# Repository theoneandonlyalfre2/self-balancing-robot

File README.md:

# Self-Balancing Robot

Robot autoequilibrado en desarrollo, con PCB propia, diseño mecánico en Fusion 360 y herramientas de control y visualización. Proyecto personal de **Alfredo Waugh Tocornal**.

Este repositorio reúne el diseño electrónico, los modelos CAD y los ensayos de firmware y software disponibles al 15 de octubre de 2026. La integración completa y la demostración de equilibrio autónomo están pendientes de validación.

*Vista del diseño CAD. No corresponde a una fotografía de un prototipo físico terminado.*

## Qué contiene

| Área | Trabajo disponible | Archivos |
|---|---|---|
| Electrónica | Esquema y PCB de dos capas en KiCad 10; ESP32-S3, TMC2209 y BNO085 en el esquema | [Proyecto KiCad](hardware/kicad), [vista de la PCB](docs/pcb-front.svg) |
| Mecánica | Base para motores NEMA 17 y encoders AS5600, plataforma para PCB, columnas y separadores | [Base de motores](mechanical/motor-base), [plataforma PCB](mechanical/pcb-deck) |
| Lectura de orientación | Firmware BNO085 y visualizador 3D de cuaterniones | [Firmware IMU](firmware/bno085), [visualizador Python](software/imu_visualizer.py) |
| Control experimental | Ensayo de control proporcional de un motor con medición de roll y ajuste desde una interfaz Qt | [Firmware de ensayo](firmware/nemamasimu), [interfaz](software/roll_controller.py) |
| Motores y encoders | Prueba independiente de dos TMC2209 y dos AS5600 con ESP32-S3 | [Prueba de banco](firmware/prueba_nema17_as5600) |
| Fabricación | Exportaciones históricas Gerber y taladros, STEP, STL y archivos Fusion 360 | [Gerbers](hardware/manufacturing), [CAD](mechanical) |

## Estado de desarrollo

- Diseño de circuito, ruteo de PCB, símbolos y huellas personalizados disponibles.
- Archivos CAD editables y exportaciones para inspeccionar la integración mecánica.
- Código de ensayos de lectura de IMU, control proporcional y movimiento de motores.
- Pendiente: unificar firmware, comprobar su correspondencia con el pinout de la PCB y validar el conjunto físico.
- Pendiente: registrar pruebas, resultados y un video del robot manteniendo el equilibrio.

Los programas son ensayos separados. `nemamasimu` describe un motor con A4988; la PCB utiliza dos TMC2209. No se ha establecido que esos ensayos puedan cargarse directamente en la PCB sin adaptar sus pines y configuración. El ensayo de dos motores tiene su propio cableado, documentado en su carpeta.

## Abrir el diseño

En **KiCad 10**, abre `hardware/kicad/Circuito Self-Balancing Robot.kicad_pro`. Se incluyen las huellas locales y dos bibliotecas de símbolos del proyecto. El esquema conserva sus símbolos embebidos. La edición de símbolos `PCM_Espressif` y los modelos 3D estándar pueden requerir instalar las bibliotecas correspondientes en tu equipo.

En **Autodesk Fusion 360**, importa los `.f3d` de `mechanical/`. Los `.step` permiten consultar la geometría en otros programas; los `.stl` corresponden a piezas individuales. Las instrucciones y dimensiones se encuentran en el `LEEME.md` de cada conjunto.

Los archivos de fabricación se conservan como exportaciones de trabajo del 5 de octubre. El PCB editable fue guardado después; no se asume que las exportaciones correspondan exactamente a su estado final. Consulta [las notas de fabricación](hardware/manufacturing/README.md).

## Usar el software

Consulta [software/README.md](software/README.md) para instalar dependencias, seleccionar el puerto serie y elegir la pareja de firmware e interfaz adecuada. El código de los ensayos se conserva sin modificar su lógica de control.

## Documentación

- [Arquitectura y protocolos](docs/architecture.md)
- [Estado y verificaciones](docs/status.md)
- [Procedencia de los archivos](docs/provenance.md)
- [Inventario con hashes SHA-256](docs/source-manifest.csv)
- [Atribuciones y componentes externos](THIRD_PARTY.md)

## Próximos hitos

1. Consolidar la asignación de pines y el firmware para la PCB.
2. Validar alimentación, sensores, drivers y mecánica del conjunto.
3. Integrar y ajustar el control de equilibrio con ambos motores.
4. Añadir registros de pruebas, fotografías del montaje y un video demostrativo.

## Autoría

Alfredo Waugh Tocornal. [LinkedIn](https://www.linkedin.com/in/alfredo-waugh-tocornal-26b0122b6).

Este repositorio no establece una licencia general de redistribución. Las bibliotecas y los diseños de terceros mantienen sus condiciones originales; consulta `THIRD_PARTY.md`.

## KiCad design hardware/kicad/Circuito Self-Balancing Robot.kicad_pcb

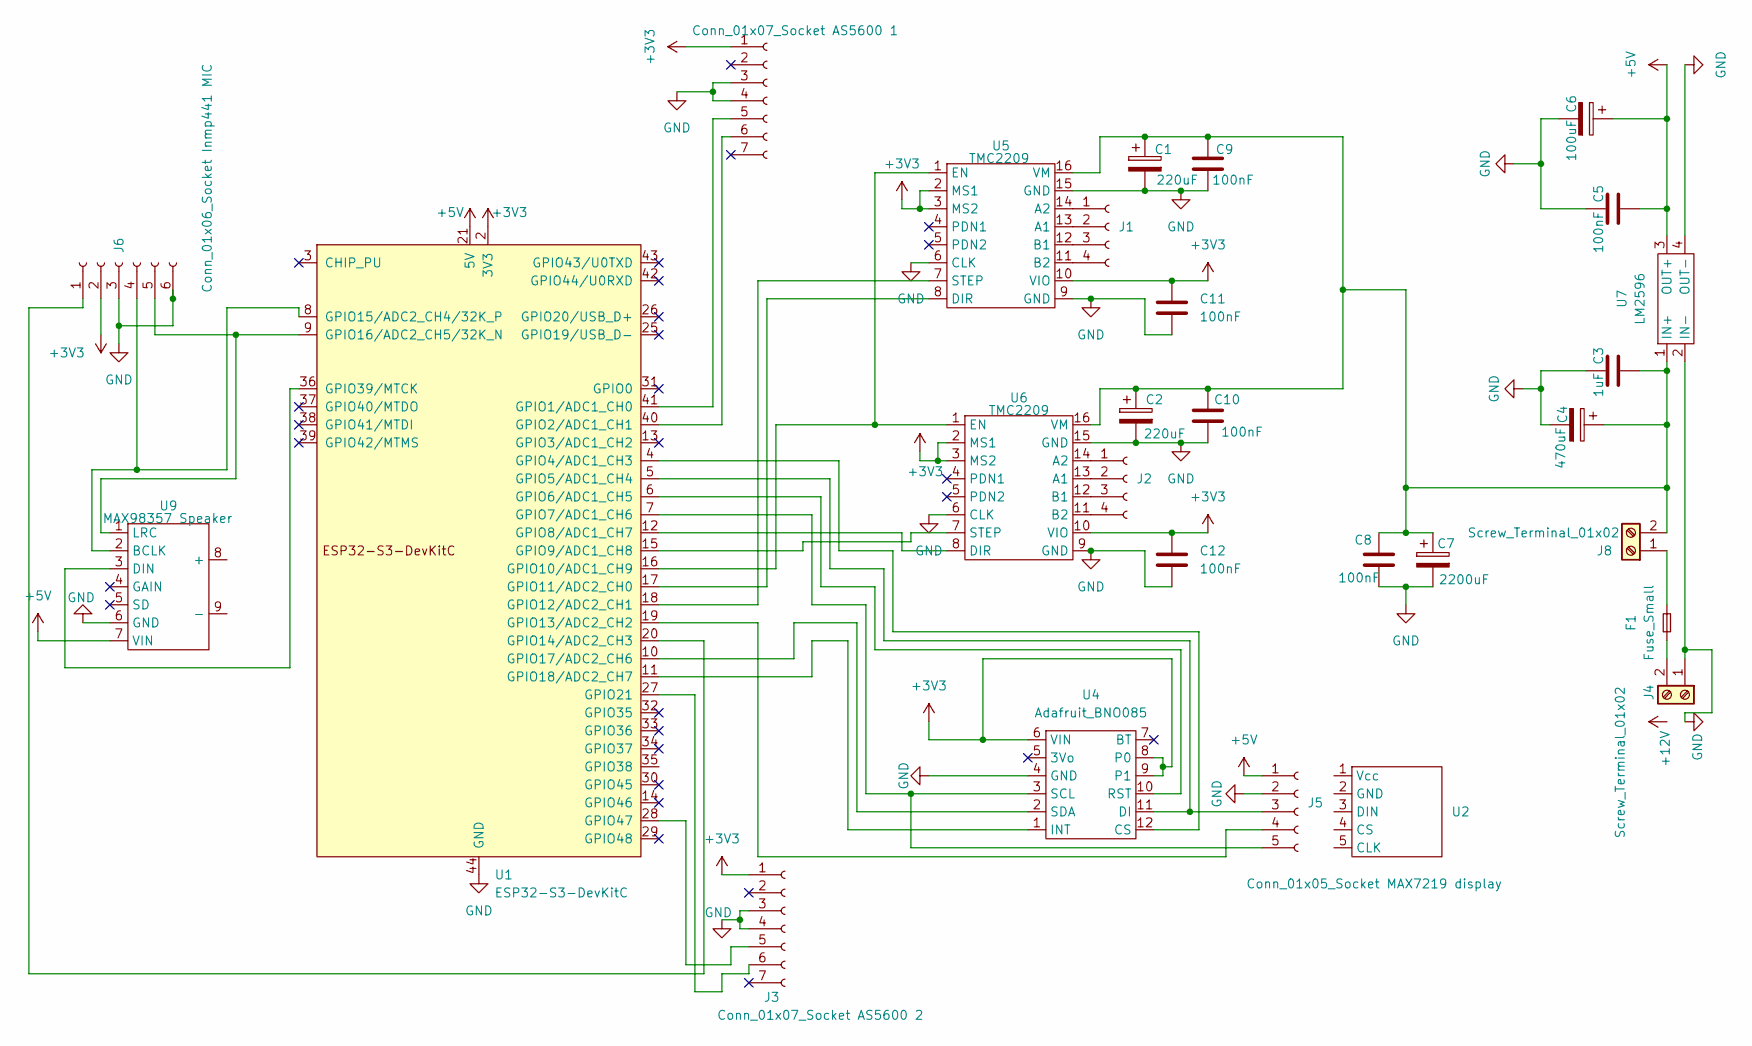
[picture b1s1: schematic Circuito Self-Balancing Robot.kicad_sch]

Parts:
C1, C2: 220uF; CP_Radial_D6.3mm_P2.50mm
C3: 1uF; C_1206_3216Metric
C4: 470uF; CP_Radial_D10.0mm_P5.00mm
C5, C8, C9, C10, C11, C12: 100nF; C_1206_3216Metric
C6: 100uF; CP_Radial_D5.0mm_P2.50mm
C7: 2200uF; CP_Radial_D16.0mm_P7.50mm
F1: Fuse_Small; Fuseholder_Blade_Mini_Keystone_3568
J1, J2: Conn_01x04_Socket; PinSocket_1x04_P2.54mm_Vertical
J3: Conn_01x07_Socket AS5600 2; PinSocket_1x07_P2.54mm_Vertical
J4, J8: Screw_Terminal_01x02; TerminalBlock_Phoenix_MKDS-1,5-2_1x02_P5.00mm_Horizontal
J5: Conn_01x05_Socket MAX7219 display; PinSocket_1x05_P2.54mm_Vertical
J6: Conn_01x06_Socket Inmp441 MIC; PinSocket_1x06_P2.54mm_Vertical
J7: Conn_01x07_Socket AS5600 1; PinSocket_1x07_P2.54mm_Vertical
U1: ESP32-S3-DevKitC
U2: 7SegmentLED_LTS6760_LTS6780
U4: Adafruit_BNO085; BNO085 footprint
U5, U6: TMC2209; Pololu_Breakout-16_15.2x20.3mm
U7: LM2596; LM2595 Footprint
U9: MAX98357 Speaker; MAX98357

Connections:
+3V3: C11.1, C12.1, J3.1, J6.2, J7.1, U1.1 (3V3), U1.2 (3V3), U4.6 (VIN), U4.8 (P0), U4.9 (P1), U5.2 (MS1), U5.3 (MS2), U5.10 (VIO), U6.2 (MS1), U6.3 (MS2), U6.10 (VIO)
+5V: C5.2, C6.1, J5.1, U1.21 (5V), U7.3 (OUT+), U9.7 (VIN)
GND: C1.2, C2.2, C3.1, C4.2, C5.1, C6.2, C7.2, C8.2, C9.2, C10.2, C11.2, C12.2, J3.3, J3.4, J4.1, J5.2, J6.3, J6.6, J7.3, J7.4, U1.22 (GND), U1.23 (GND), U1.24 (GND), U1.44 (GND), U4.4 (GND), U5.6 (CLK), U5.9 (GND), U5.15 (GND), U6.6 (CLK), U6.9 (GND), U6.15 (GND), U7.2 (IN-), U7.4 (OUT-), U9.6 (GND)
unnamed: J1.1, U5.14 (A2)
unnamed: J1.2, U5.13 (A1)
unnamed: J1.3, U5.12 (B1)
unnamed: J1.4, U5.11 (B2)
unnamed: J2.1, U6.14 (A2)
unnamed: J2.2, U6.13 (A1)
unnamed: J2.3, U6.12 (B1)
unnamed: J2.4, U6.11 (B2)
unnamed: J3.5, U1.28 (GPIO47)
unnamed: J3.6, U1.27 (GPIO21)
unnamed: F1.1, J4.2
unnamed: J5.3, U1.5 (GPIO5/ADC1_CH4), U4.11 (DI)
unnamed: J5.4, U1.19 (GPIO13/ADC2_CH2)
unnamed: J5.5, U1.7 (GPIO7/ADC1_CH6), U4.3 (SCL)
unnamed: J6.1, U1.20 (GPIO14/ADC2_CH3)
unnamed: J6.4, U1.8 (GPIO15/ADC2_CH4/32K_P), U9.2 (BCLK)
unnamed: J6.5, U1.9 (GPIO16/ADC2_CH5/32K_N), U9.1 (LRC)
unnamed: J7.5, U1.41 (GPIO1/ADC1_CH0)
unnamed: J7.6, U1.40 (GPIO2/ADC1_CH1)
unnamed: F1.2, J8.1
unnamed: C1.1, C2.1, C3.2, C4.1, C7.1, C8.1, C9.1, C10.1, J8.2, U5.16 (VM), U6.16 (VM), U7.1 (IN+)
unnamed: U1.4 (GPIO4/ADC1_CH3), U4.12 (CS)
unnamed: U1.6 (GPIO6/ADC1_CH5), U4.10 (RST)
unnamed: U1.12 (GPIO8/ADC1_CH7), U6.8 (DIR)
unnamed: U1.15 (GPIO9/ADC1_CH8), U6.7 (STEP)
unnamed: U1.16 (GPIO10/ADC1_CH9), U5.1 (EN), U6.1 (EN)
unnamed: U1.17 (GPIO11/ADC2_CH0), U5.8 (DIR)
unnamed: U1.18 (GPIO12/ADC2_CH1), U5.7 (STEP)
unnamed: U1.10 (GPIO17/ADC2_CH6), U4.2 (SDA)
unnamed: U1.11 (GPIO18/ADC2_CH7), U4.1 (INT)
unnamed: U1.36 (GPIO39/MTCK), U9.3 (DIN)

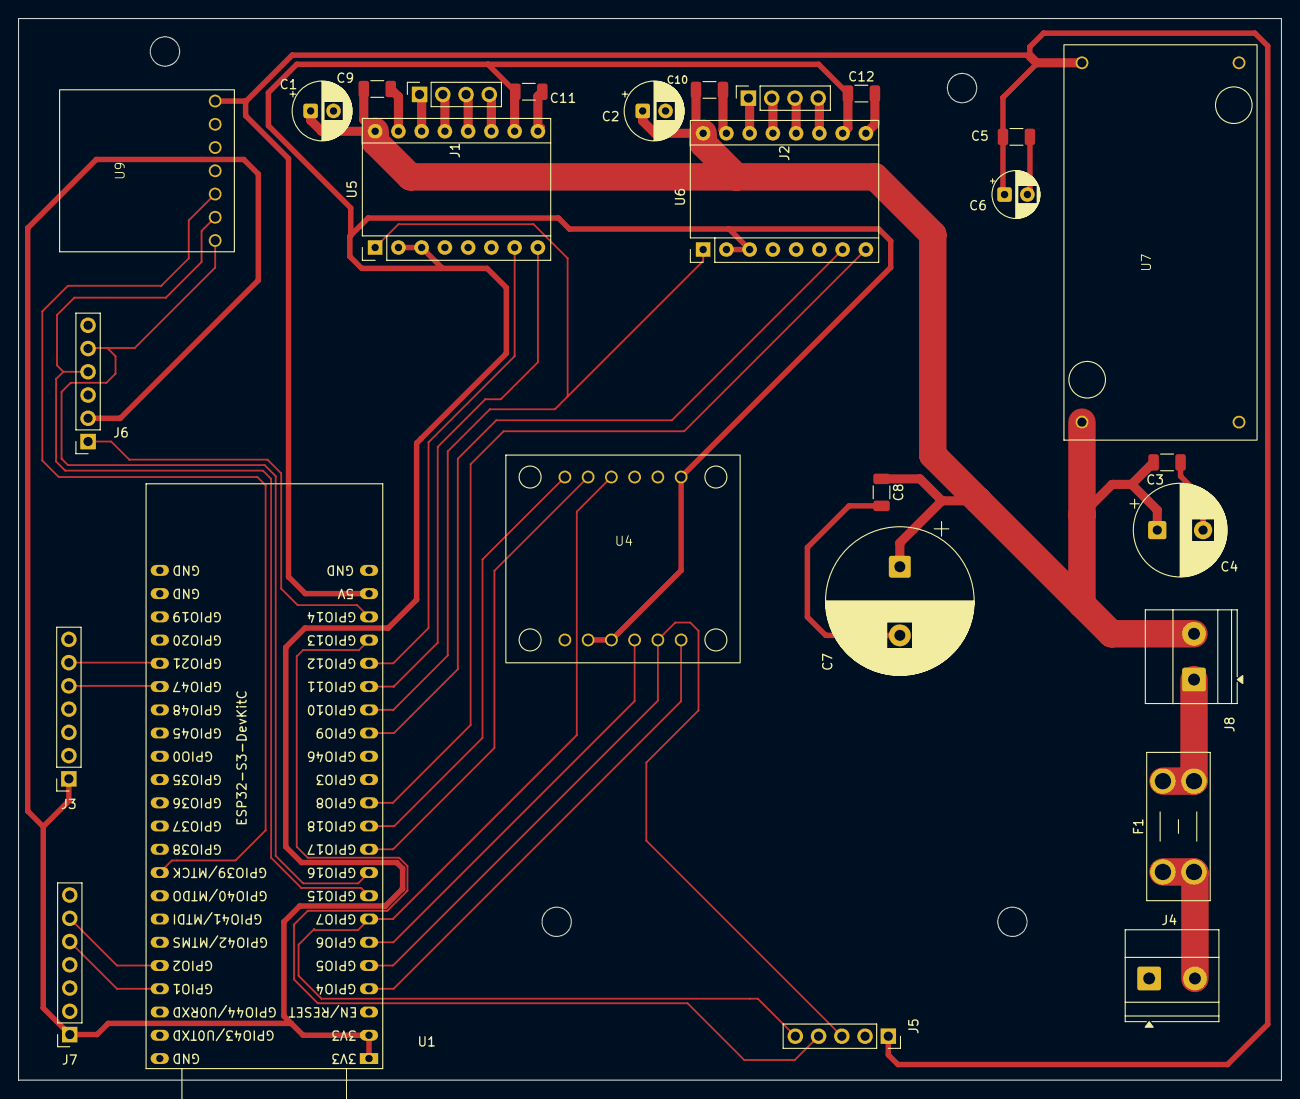
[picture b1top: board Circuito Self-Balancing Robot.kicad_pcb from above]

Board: 2 copper layers, 138.0 x 116.0 mm, 27 parts (0 on the bottom side), 34 nets.

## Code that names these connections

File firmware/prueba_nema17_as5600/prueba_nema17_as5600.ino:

/*
  Prueba de banco: ESP32-S3 DevKitC, 2 TMC2209 y 2 AS5600.
  Arduino IDE con paquete esp32 de Espressif. Wire viene incluido.
  TMC2209 en modo standalone STEP/DIR. No requiere UART ni multiplexor.

  Motor 1: STEP GPIO4, DIR GPIO5, ENABLE GPIO6.
  Motor 2: STEP GPIO15, DIR GPIO16, ENABLE GPIO17.
  AS5600 motor 1: SDA GPIO8, SCL GPIO9 (Wire).
  AS5600 motor 2: SDA GPIO10, SCL GPIO11 (Wire1).
  Logica y buses I2C a 3.3 V. Alimentacion de motores externa.
  Ambos TMC2209: MS1 y MS2 a 3.3 V, SPREAD a GND: 1/16 de paso.
  PDN_UART a GND en esta prueba standalone; DIAG e INDEX sin conectar.

  Monitor serie: 115200 baudios.
  '1' prueba motor 1; '2' prueba motor 2; 's' interrumpe el movimiento.
  Cada prueba ordena 90 grados y luego 90 grados en sentido contrario.
  Los angulos se imprimen continuamente cuando los motores estan libres.

  Ajustar el limite de corriente de cada driver antes de conectar motores.
  Usar motores sin carga y con espacio para girar. No conectar ni desconectar
  motores con alimentacion. Esta prueba mide; no corrige posicion por encoder.
*/

#include <Wire.h>

const uint8_t STEP_PIN[2] = {4, 15};
const uint8_t DIR_PIN[2]  = {5, 16};
const uint8_t EN_PIN[2]   = {6, 17};
const uint8_t AS_ADDR  = 0x36;
bool busListo[2] = {false, false};

// Revisar la ficha de cada motor: 200 para 1.8 grados; 400 para 0.9 grados.
// Son pasos completos por vuelta, SIN multiplicar por los micropasos.
const uint16_t PASOS_VUELTA[2] = {200, 200};
const uint16_t MICROPASOS = 16; // MS1=HIGH y MS2=HIGH en ambos TMC2209.

// Lee STATUS (0x0B) y RAW ANGLE (0x0C, 0x0D).
// Cada encoder tiene su propio controlador I2C, ambos con direccion 0x36.
bool leerEncoder(uint8_t motor, float &angulo) {
  Serial.print(F("Encoder "));
  Serial.print(motor + 1);
  Serial.print(F(": "));

  if (!busListo[motor]) {
    Serial.println(F("ERROR: bus I2C no inicializado"));
    return false;
  }

  TwoWire &bus = (motor == 0) ? Wire : Wire1;
  bus.beginTransmission(AS_ADDR);
  bus.write((uint8_t)0x0B);
  if (bus.endTransmission(false) != 0) {
    Serial.println(F("ERROR: AS5600 no responde"));
    return false;
  }
  if (bus.requestFrom(AS_ADDR, (size_t)3) != 3) {
    Serial.println(F("ERROR: lectura I2C incompleta"));
    return false;
  }

  uint8_t estado = bus.read();
  uint16_t raw = (uint16_t)(bus.read() & 0x0F) << 8;
  raw |= (uint8_t)bus.read();
  bool imanCorrecto = (estado & 0x38) == 0x20;

  if (!(estado & 0x20)) Serial.print(F("IMAN NO DETECTADO "));
  if (estado & 0x10) Serial.print(F("CAMPO DEBIL "));
  if (estado & 0x08) Serial.print(F("CAMPO FUERTE "));
  if (!imanCorrecto) {
    Serial.println();
    return false;
  }

  angulo = raw * (360.0f / 4096.0f);
  Serial.print(angulo, 2);
  Serial.println(F(" grados; iman OK"));
  return true;
}

// Diferencia con correccion del cruce 359 -> 0 grados.
// Adecuada para esta prueba de 90 grados; no cuenta vueltas completas.
float diferencia(float finalAngulo, float inicioAngulo) {
  float d = finalAngulo - inicioAngulo;
  if (d > 180.0f) d -= 360.0f;
  if (d < -180.0f) d += 360.0f;
  return d;
}

bool moverCuarto(uint8_t motor, bool sentido) {
  digitalWrite(DIR_PIN[motor], sentido ? HIGH : LOW);
  delayMicroseconds(10);
  const uint32_t pasos = (uint32_t)PASOS_VUELTA[motor] * MICROPASOS / 4;
  for (uint32_t i = 0; i < pasos; ++i) {
    while (Serial.available()) {
      char c = Serial.read();
      if (c == 's' || c == 'S') {
        Serial.println(F("Prueba interrumpida; no se ordena regreso."));
        return false;
      }
    }
    digitalWrite(STEP_PIN[motor], HIGH);
    delayMicroseconds(5);
    digitalWrite(STEP_PIN[motor], LOW);
    delay(1); // Aproximadamente 1000 micropasos/s o menos, sin carga.
  }
  delay(150); // Espera a que el eje y la lectura se estabilicen.
  return true;
}

void probarMotor(uint8_t motor) {
  float inicial, anterior, actual;
  Serial.print(F("\nPRUEBA MOTOR "));
  Serial.println(motor + 1);
  if (!leerEncoder(motor, inicial)) return;

  digitalWrite(EN_PIN[motor], LOW); // TMC2209 habilitado con nivel bajo.
  delay(500); // Alineacion inicial y establecimiento de corriente.
  if (!leerEncoder(motor, inicial)) {
    digitalWrite(EN_PIN[motor], HIGH);
    return;
  }
  anterior = inicial;

  for (uint8_t tramo = 0; tramo < 2; ++tramo) {
    Serial.println(tramo == 0 ? F("Ida: 90 grados") : F("Regreso: 90 grados"));
    if (!moverCuarto(motor, tramo == 0)) break;
    if (!leerEncoder(motor, actual)) {
      Serial.println(F("Prueba detenida por error del encoder."));
      break;
    }
    Serial.print(F("Giro medido en este tramo: "));
    Serial.print(diferencia(actual, anterior), 2);
    Serial.println(F(" grados"));
    anterior = actual;
    if (tramo == 1) {
      Serial.print(F("Desviacion respecto al inicio: "));
      Serial.print(diferencia(actual, inicial), 2);
      Serial.println(F(" grados (esperado: cerca de 0)"));
    }
    delay(400);
  }

  digitalWrite(EN_PIN[motor], HIGH);
  Serial.println(F("Motor deshabilitado. Comandos: 1 o 2."));
}

void setup() {
  for (uint8_t m = 0; m < 2; ++m) {
    digitalWrite(EN_PIN[m], HIGH);
    pinMode(EN_PIN[m], OUTPUT);
    digitalWrite(STEP_PIN[m], LOW);
    pinMode(STEP_PIN[m], OUTPUT);
    digitalWrite(DIR_PIN[m], LOW);
    pinMode(DIR_PIN[m], OUTPUT);
  }
  Serial.begin(115200);
  busListo[0] = Wire.begin(8, 9, 100000);
  busListo[1] = Wire1.begin(10, 11, 100000);
  Wire.setTimeOut(25);
  Wire1.setTimeOut(25);
  delay(1000);
  Serial.println(F("ESP32-S3 + TMC2209 + AS5600."));
  Serial.println(F("Envia 1 o 2 para probar; s para parar."));
}

void loop() {
  if (Serial.available()) {
    char c = Serial.read();
    if (c == '1' || c == '2') probarMotor(c - '1');
  }

  static unsigned long ultimoReporte = 0;
  if (millis() - ultimoReporte >= 1000) {
    ultimoReporte = millis();
    float angulo;
    leerEncoder(0, angulo);
    leerEncoder(1, angulo);
  }
  delay(1);
}
